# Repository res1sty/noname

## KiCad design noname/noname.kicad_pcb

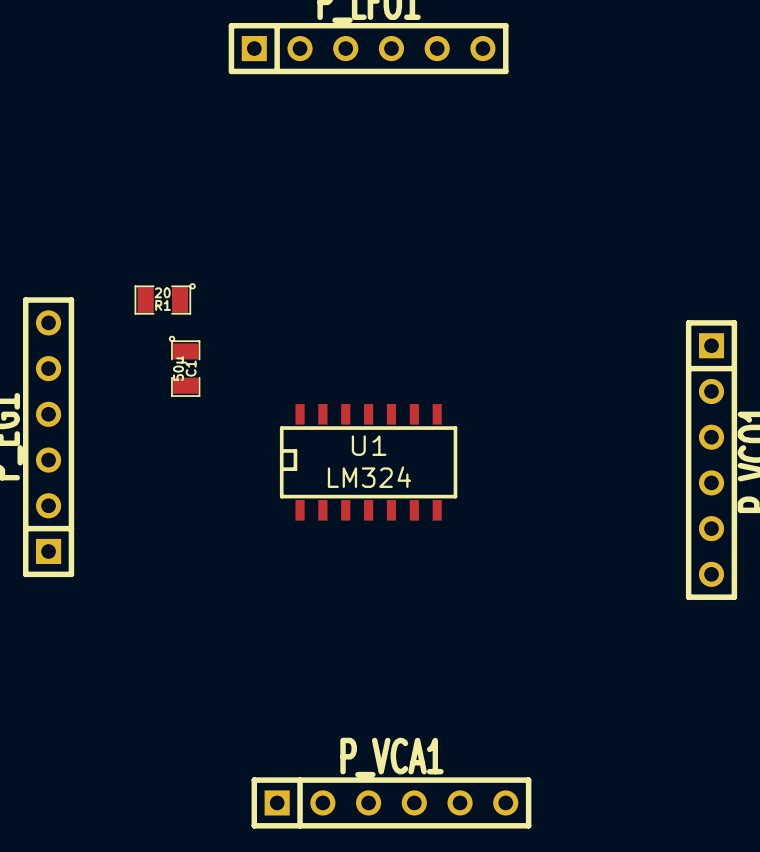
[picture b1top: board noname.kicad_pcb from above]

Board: 2 copper layers, 7 parts (0 on the bottom side), 7 nets, no tracks yet.

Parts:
C1: 50µ; SM0805
P_EG1: CONN_6; SIL-6
P_LFO1: CONN_6; SIL-6
P_VCA1: CONN_6; SIL-6
P_VCO1: CONN_6; SIL-6
R1: 20; SM0805
U1: LM324; SO14E

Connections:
unnamed: C1.2, P_EG1.6, R1.2
unnamed: P_EG1.4, U1.14
unnamed: P_EG1.1, U1.4
unnamed: C1.1, R1.1
unnamed: P_LFO1.2, U1.11
unnamed: P_LFO1.1, U1.1
unnamed: P_LFO1.3, U1.2

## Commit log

2014-10-17 kicad tests
2014-10-17 initial bom
